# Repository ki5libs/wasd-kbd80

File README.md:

# WASD-kbd80

80% mechanical switch keyboard

## Goal Features
 - QMK-compatibility
 - WASD-libre controller compatibility
 - Mechanical compatibility with existing popular 80% keyboards (i.e XD87 from KRepublic)
 - ANSI, ISO and JIS layouts on one PCB
 - Regulated backlight
 - RGB-highlight
 
 The work is in progress...

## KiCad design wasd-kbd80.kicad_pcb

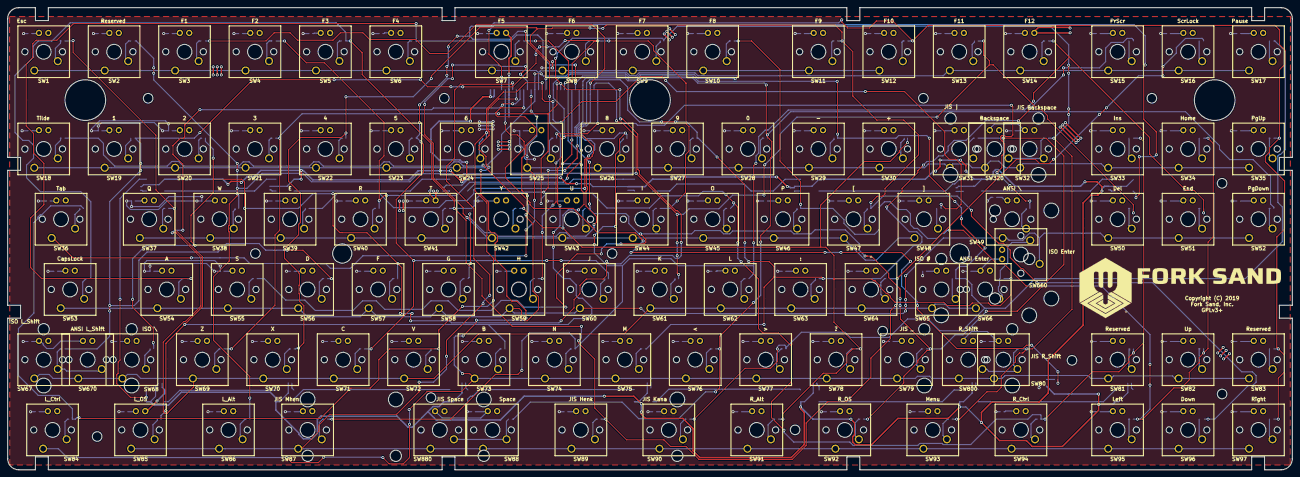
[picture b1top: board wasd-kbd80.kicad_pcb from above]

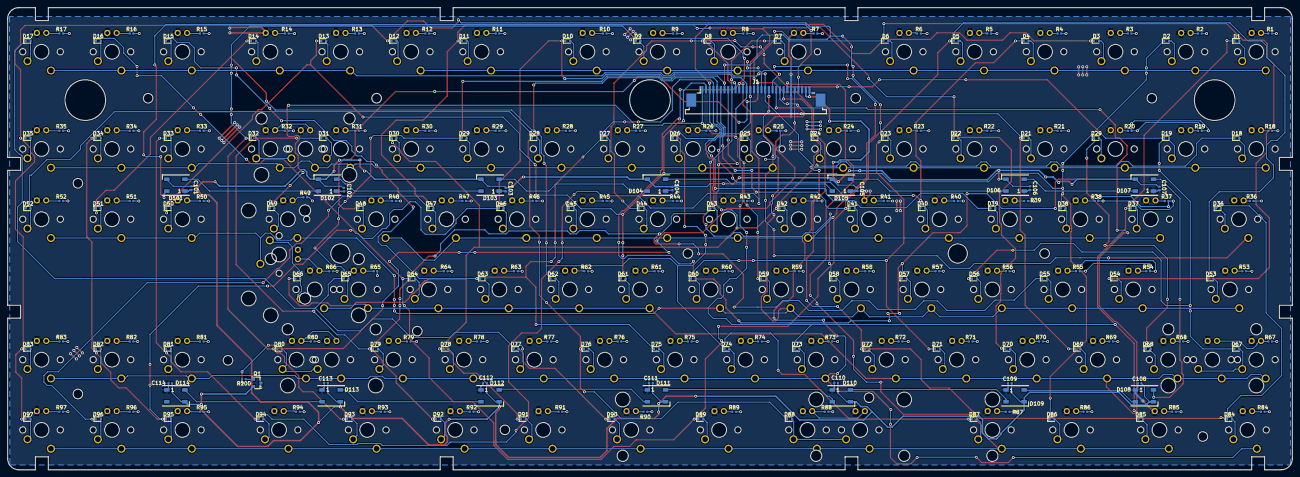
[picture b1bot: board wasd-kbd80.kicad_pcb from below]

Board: 2 copper layers, 347.5 x 125.0 mm, 327 parts (225 on the bottom side), 237 nets.

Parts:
C101, C102, C103, C104, C105, C106, C107, C108, C109, C110, C111, C112, C113, C114: 15pF; C_0402_1005Metric
D1, D2, D3, D4, D5, D6, D7, D8, D9, D10, D11, D12, D13, D14, D15, D16, D17, D18, D19, D20, D21, D22, D23, D24, D25, D26, D27, D28, D29, D30, D31, D32, D33, D34, D35, D36, D37, D38, D39, D40, D41, D42, D43, D44, D45, D46, D47, D48, D49, D50, D51, D52, D53, D54, D55, D56, D57, D58, D59, D60, D61, D62, D63, D64, D65, D66, D67, D68, D69, D70, D71, D72, D73, D74, D75, D76, D77, D78, D79, D80, D81, D82, D83, D84, D85, D86, D87, D88, D89, D90, D91, D92, D93, D94, D95, D96, D97: 1N4148WT; D_SOD-523
D101, D102, D103, D104, D105, D106, D107, D108, D109, D110, D111, D112, D113, D114: WS2812B; LED_WS2812B_PLCC4_5.0x5.0mm_P3.2mm
J1: Conn_01x30; TE_3-84953-0_1x30-1MP_P1.0mm_Horizontal
Q1: BC817; SOT-23
R1, R2, R3, R4, R5, R6, R7, R8, R9, R10, R11, R12, R13, R14, R15, R16, R17, R18, R19, R20, R21, R22, R23, R24, R25, R26, R27, R28, R29, R30, R31, R32, R33, R34, R35, R36, R37, R38, R39, R40, R41, R42, R43, R44, R45, R46, R47, R48, R49, R50, R51, R52, R53, R54, R55, R56, R57, R58, R59, R60, R61, R62, R63, R64, R65, R66, R67, R68, R69, R70, R71, R72, R73, R74, R75, R76, R77, R78, R79, R80, R81, R82, R83, R84, R85, R86, R87, R88, R89, R90, R91, R92, R93, R94, R95, R96, R97: 330R; R_0402_1005Metric
R200: 3K3; R_0402_1005Metric
SW1: Esc; SW_Cherry_MX_1.00u_PCB_LED
SW2, SW81, SW83: Reserved; SW_Cherry_MX_1.00u_PCB_LED
SW3: F1; SW_Cherry_MX_1.00u_PCB_LED
SW4: F2; SW_Cherry_MX_1.00u_PCB_LED
SW5: F3; SW_Cherry_MX_1.00u_PCB_LED
SW6: F4; SW_Cherry_MX_1.00u_PCB_LED
SW7: F5; SW_Cherry_MX_1.00u_PCB_LED
SW8: F6; SW_Cherry_MX_1.00u_PCB_LED
SW9: F7; SW_Cherry_MX_1.00u_PCB_LED
SW10: F8; SW_Cherry_MX_1.00u_PCB_LED
SW11: F9; SW_Cherry_MX_1.00u_PCB_LED
SW12: F10; SW_Cherry_MX_1.00u_PCB_LED
SW13: F11; SW_Cherry_MX_1.00u_PCB_LED
SW14: F12; SW_Cherry_MX_1.00u_PCB_LED
SW15: PrScr; SW_Cherry_MX_1.00u_PCB_LED
SW16: ScrLock; SW_Cherry_MX_1.00u_PCB_LED
SW17: Pause; SW_Cherry_MX_1.00u_PCB_LED
SW18: Tilde; SW_Cherry_MX_1.00u_PCB_LED
SW19: 1; SW_Cherry_MX_1.00u_PCB_LED
SW20: 2; SW_Cherry_MX_1.00u_PCB_LED
SW21: 3; SW_Cherry_MX_1.00u_PCB_LED
SW22: 4; SW_Cherry_MX_1.00u_PCB_LED
SW23: 5; SW_Cherry_MX_1.00u_PCB_LED
SW24: 6; SW_Cherry_MX_1.00u_PCB_LED
SW25: 7; SW_Cherry_MX_1.00u_PCB_LED
SW26: 8; SW_Cherry_MX_1.00u_PCB_LED
SW27: 9; SW_Cherry_MX_1.00u_PCB_LED
SW28: 0; SW_Cherry_MX_1.00u_PCB_LED
SW29: -; SW_Cherry_MX_1.00u_PCB_LED
SW30: +; SW_Cherry_MX_1.00u_PCB_LED
SW31: JIS |; SW_Cherry_MX_1.00u_PCB_LED
SW32: JIS Backspace; SW_Cherry_MX_1.00u_PCB_LED
SW33: Ins; SW_Cherry_MX_1.00u_PCB_LED
SW34: Home; SW_Cherry_MX_1.00u_PCB_LED
SW35: PgUp; SW_Cherry_MX_1.00u_PCB_LED
SW36: Tab; SW_Cherry_MX_1.50u_PCB_LED
SW37: Q; SW_Cherry_MX_1.00u_PCB_LED
SW38: W; SW_Cherry_MX_1.00u_PCB_LED
SW39: E; SW_Cherry_MX_1.00u_PCB_LED
SW40: R; SW_Cherry_MX_1.00u_PCB_LED
SW41: T; SW_Cherry_MX_1.00u_PCB_LED
SW42: Y; SW_Cherry_MX_1.00u_PCB_LED
SW43: U; SW_Cherry_MX_1.00u_PCB_LED
SW44: I; SW_Cherry_MX_1.00u_PCB_LED
SW45: O; SW_Cherry_MX_1.00u_PCB_LED
SW46: P; SW_Cherry_MX_1.00u_PCB_LED
SW47: [; SW_Cherry_MX_1.00u_PCB_LED
SW48: ]; SW_Cherry_MX_1.00u_PCB_LED
SW49: ANSI \; SW_Cherry_MX_1.50u_PCB_LED
SW50: Del; SW_Cherry_MX_1.00u_PCB_LED
SW51: End; SW_Cherry_MX_1.00u_PCB_LED
SW52: PgDown; SW_Cherry_MX_1.00u_PCB_LED
SW53: CapsLock; SW_Cherry_MX_1.75u_PCB_LED
SW54: A; SW_Cherry_MX_1.00u_PCB_LED
SW55: S; SW_Cherry_MX_1.00u_PCB_LED
SW56: D; SW_Cherry_MX_1.00u_PCB_LED
SW57: F; SW_Cherry_MX_1.00u_PCB_LED
SW58: G; SW_Cherry_MX_1.00u_PCB_LED
SW59: H; SW_Cherry_MX_1.00u_PCB_LED
SW60: J; SW_Cherry_MX_1.00u_PCB_LED
SW61: K; SW_Cherry_MX_1.00u_PCB_LED
SW62: L; SW_Cherry_MX_1.00u_PCB_LED
SW63: :; SW_Cherry_MX_1.00u_PCB_LED
SW64: "; SW_Cherry_MX_1.00u_PCB_LED
SW65: ISO #; SW_Cherry_MX_1.00u_PCB_LED
SW66: ANSI Enter; SW_Cherry_MX_2.25u_PCB_LED_Inv
SW67: ISO L_Shift; SW_Cherry_MX_1.00u_PCB_LED
SW68: ISO \; SW_Cherry_MX_1.00u_PCB_LED
SW69: Z; SW_Cherry_MX_1.00u_PCB_LED
SW70: X; SW_Cherry_MX_1.00u_PCB_LED
SW71: C; SW_Cherry_MX_1.00u_PCB_LED
SW72: V; SW_Cherry_MX_1.00u_PCB_LED
SW73: B; SW_Cherry_MX_1.00u_PCB_LED
SW74: N; SW_Cherry_MX_1.00u_PCB_LED
SW75: M; SW_Cherry_MX_1.00u_PCB_LED
SW76: <; SW_Cherry_MX_1.00u_PCB_LED
SW77: >; SW_Cherry_MX_1.00u_PCB_LED
SW78: ?; SW_Cherry_MX_1.00u_PCB_LED
SW79: JIS _; SW_Cherry_MX_1.00u_PCB_LED
SW80: JIS R_Shift; SW_Cherry_MX_1.75u_PCB_LED
SW82: Up; SW_Cherry_MX_1.00u_PCB_LED
SW84: L_Ctrl; SW_Cherry_MX_1.25u_PCB_LED
SW85: L_OS; SW_Cherry_MX_1.25u_PCB_LED
SW86: L_Alt; SW_Cherry_MX_1.25u_PCB_LED
SW87: JIS Mhen; SW_Cherry_MX_1.00u_PCB_LED
SW88: Space; SW_Cherry_MX_6.25u_PCB_LED
SW89: JIS Henk; SW_Cherry_MX_1.25u_PCB_LED
SW90: JIS Kana; SW_Cherry_MX_1.25u_PCB_LED
SW91: R_Alt; SW_Cherry_MX_1.25u_PCB_LED
SW92: R_OS; SW_Cherry_MX_1.25u_PCB_LED
SW93: Menu; SW_Cherry_MX_1.25u_PCB_LED
SW94: R_Ctrl; SW_Cherry_MX_1.25u_PCB_LED
SW95: Left; SW_Cherry_MX_1.00u_PCB_LED
SW96: Down; SW_Cherry_MX_1.00u_PCB_LED
SW97: Right; SW_Cherry_MX_1.00u_PCB_LED
SW320: Backspace; SW_Cherry_MX_2.00u_PCB_LED_Inv
SW660: ISO Enter; SW_Cherry_MX_ISOEnter_PCB_LED_Rot
SW670: ANSI L_Shift; SW_Cherry_MX_2.25u_PCB_LED_Inv
SW800: R_Shift; SW_Cherry_MX_2.75u_PCB_LED_Inv
SW880: JIS Space; SW_Cherry_MX_2.75u_PCB_LED

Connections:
+5V: C101.2, C102.2, C103.2, C104.2, C105.2, C106.2, C107.2, C108.2, C109.2, C110.2, C111.2, C112.2, C113.2, C114.2, D101.1, D102.1, D103.1, D104.1, D105.1, D106.1, D107.1, D108.1, D109.1, D110.1, D111.1, D112.1, D113.1, D114.1, J1.25, J1.28, SW1.4, SW2.4, SW3.4, SW4.4, SW5.4, SW6.4, SW7.4, SW8.4, SW9.4, SW10.4, SW11.4, SW12.4, SW13.4, SW14.4, SW15.4, SW16.4, SW17.4, SW18.4, SW19.4, SW20.4, SW21.4, SW22.4, SW23.4, SW24.4, SW25.4, SW26.4, SW27.4, SW28.4, SW29.4, SW30.4, SW31.4, SW32.4, SW33.4, SW34.4, SW35.4, SW36.4, SW37.4, SW38.4, SW39.4, SW40.4, SW41.4, SW42.4, SW43.4, SW44.4, SW45.4, SW46.4, SW47.4, SW48.4, SW49.4, SW50.4, SW51.4, SW52.4, SW53.4, SW54.4, SW55.4, SW56.4, SW57.4, SW58.4, SW59.4, SW60.4, SW61.4, SW62.4, SW63.4, SW64.4, SW65.4, SW66.4, SW67.4, SW68.4, SW69.4, SW70.4, SW71.4, SW72.4, SW73.4, SW74.4, SW75.4, SW76.4, SW77.4, SW78.4, SW79.4, SW80.4, SW81.4, SW82.4, SW83.4, SW84.4, SW85.4, SW86.4, SW87.4, SW88.4, SW89.4, SW90.4, SW91.4, SW92.4, SW93.4, SW94.4, SW95.4, SW96.4, SW97.4, SW320.4, SW660.4, SW670.4, SW800.4, SW880.4
/32D: D32.2, SW32.2, SW320.2
/32LED: R32.1, SW32.3, SW320.3
/66D: D66.2, SW66.2, SW660.2
/66LED: R66.1, SW66.3, SW660.3
/67D: D67.2, SW67.2, SW670.2
/67LED: R67.1, SW67.3, SW670.3
/80D: D80.2, SW80.2, SW800.2
/80LED: R80.1, SW80.3, SW800.3
/88D: D88.2, SW88.2, SW880.2
/88LED: R88.1, SW88.3, SW880.3
/COL0: J1.17, SW1.1, SW2.1, SW3.1, SW4.1, SW5.1, SW6.1, SW7.1, SW8.1, SW9.1, SW10.1, SW11.1, SW12.1
/COL1: J1.18, SW13.1, SW14.1, SW15.1, SW16.1, SW17.1, SW18.1, SW19.1, SW20.1, SW21.1, SW22.1, SW23.1, SW24.1
/COL2: J1.19, SW25.1, SW26.1, SW27.1, SW28.1, SW29.1, SW30.1, SW31.1, SW32.1, SW33.1, SW34.1, SW35.1, SW36.1, SW320.1
/COL3: J1.20, SW37.1, SW38.1, SW39.1, SW40.1, SW41.1, SW42.1, SW43.1, SW44.1, SW45.1, SW46.1, SW47.1, SW48.1
/COL4: J1.21, SW49.1, SW50.1, SW51.1, SW52.1, SW53.1, SW54.1, SW55.1, SW56.1, SW57.1, SW58.1, SW59.1, SW60.1, SW660.1
/COL5: J1.22, SW61.1, SW62.1, SW63.1, SW64.1, SW65.1, SW66.1, SW67.1, SW68.1, SW69.1, SW70.1, SW71.1, SW72.1, SW670.1
/COL6: J1.23, SW73.1, SW74.1, SW75.1, SW76.1, SW77.1, SW78.1, SW79.1, SW80.1, SW81.1, SW82.1, SW83.1, SW84.1, SW800.1
/COL7: J1.24, SW85.1, SW86.1, SW87.1, SW88.1, SW89.1, SW90.1, SW91.1, SW92.1, SW93.1, SW94.1, SW95.1, SW96.1, SW97.1, SW880.1
/LED_DRV: Q1.3, R1.2, R2.2, R3.2, R4.2, R5.2, R6.2, R7.2, R8.2, R9.2, R10.2, R11.2, R12.2, R13.2, R14.2, R15.2, R16.2, R17.2, R18.2, R19.2, R20.2, R21.2, R22.2, R23.2, R24.2, R25.2, R26.2, R27.2, R28.2, R29.2, R30.2, R31.2, R32.2, R33.2, R34.2, R35.2, R36.2, R37.2, R38.2, R39.2, R40.2, R41.2, R42.2, R43.2, R44.2, R45.2, R46.2, R47.2, R48.2, R49.2, R50.2, R51.2, R52.2, R53.2, R54.2, R55.2, R56.2, R57.2, R58.2, R59.2, R60.2, R61.2, R62.2, R63.2, R64.2, R65.2, R66.2, R67.2, R68.2, R69.2, R70.2, R71.2, R72.2, R73.2, R74.2, R75.2, R76.2, R77.2, R78.2, R79.2, R80.2, R81.2, R82.2, R83.2, R84.2, R85.2, R86.2, R87.2, R88.2, R89.2, R90.2, R91.2, R92.2, R93.2, R94.2, R95.2, R96.2, R97.2
/PWM_IN: J1.26, R200.2
/RGB_IN: D101.4, J1.27
/ROW0: D1.1, D25.1, D37.1, D49.1, D73.1, D85.1, J1.1
/ROW1: D2.1, D13.1, D38.1, D50.1, D61.1, D86.1, J1.2
/ROW2: D3.1, D14.1, D26.1, D51.1, D62.1, D74.1, D87.1, J1.3
/ROW3: D15.1, D27.1, D39.1, D63.1, D75.1, J1.4
/ROW4: D4.1, D28.1, D40.1, D52.1, D76.1, D88.1, J1.5
/ROW5: D5.1, D16.1, D41.1, D53.1, D64.1, D89.1, J1.6
/ROW6: D6.1, D17.1, D29.1, D54.1, D65.1, D77.1, D90.1, J1.7
/ROW7: D18.1, D30.1, D42.1, D66.1, D78.1, D91.1, J1.8
/ROW8: D7.1, D31.1, D43.1, D55.1, D79.1, D92.1, J1.9
/ROW9: D8.1, D19.1, D44.1, D56.1, D67.1, J1.10
/ROW10: D9.1, D20.1, D32.1, D57.1, D68.1, D80.1, D93.1, J1.11
/ROW11: D21.1, D33.1, D45.1, D69.1, D81.1, D94.1, J1.12
/ROW12: D10.1, D34.1, D46.1, D58.1, D82.1, D95.1, J1.13
/ROW13: D11.1, D22.1, D47.1, D59.1, D70.1, D96.1, J1.14
/ROW14: D12.1, D23.1, D35.1, D60.1, D71.1, D83.1, D97.1, J1.15
/ROW15: D24.1, D36.1, D48.1, D72.1, D84.1, J1.16
GND: C101.1, C102.1, C103.1, C104.1, C105.1, C106.1, C107.1, C108.1, C109.1, C110.1, C111.1, C112.1, C113.1, C114.1, D101.3, D102.3, D103.3, D104.3, D105.3, D106.3, D107.3, D108.3, D109.3, D110.3, D111.3, D112.3, D113.3, D114.3, J1.29, J1.30, Q1.2
unnamed: D1.2, SW1.2
unnamed: D2.2, SW2.2
unnamed: D3.2, SW3.2
unnamed: D4.2, SW4.2
unnamed: D5.2, SW5.2
unnamed: D6.2, SW6.2
unnamed: D7.2, SW7.2
unnamed: D8.2, SW8.2
unnamed: D9.2, SW9.2
unnamed: D10.2, SW10.2
unnamed: D11.2, SW11.2
unnamed: D12.2, SW12.2
unnamed: D13.2, SW13.2
unnamed: D14.2, SW14.2
unnamed: D15.2, SW15.2
unnamed: D16.2, SW16.2
unnamed: D17.2, SW17.2
unnamed: D18.2, SW18.2
unnamed: D19.2, SW19.2
unnamed: D20.2, SW20.2
unnamed: D21.2, SW21.2
unnamed: D22.2, SW22.2
unnamed: D23.2, SW23.2
unnamed: D24.2, SW24.2
unnamed: D25.2, SW25.2
unnamed: D26.2, SW26.2
unnamed: D27.2, SW27.2
unnamed: D28.2, SW28.2
unnamed: D29.2, SW29.2
unnamed: D30.2, SW30.2
unnamed: D31.2, SW31.2
unnamed: D33.2, SW33.2
unnamed: D34.2, SW34.2
unnamed: D35.2, SW35.2
unnamed: D36.2, SW36.2
unnamed: D37.2, SW37.2
unnamed: D38.2, SW38.2
unnamed: D39.2, SW39.2
unnamed: D40.2, SW40.2
unnamed: D41.2, SW41.2
unnamed: D42.2, SW42.2
unnamed: D43.2, SW43.2
unnamed: D44.2, SW44.2
unnamed: D45.2, SW45.2
unnamed: D46.2, SW46.2
unnamed: D47.2, SW47.2
unnamed: D48.2, SW48.2
unnamed: D49.2, SW49.2
unnamed: D50.2, SW50.2
unnamed: D51.2, SW51.2
unnamed: D52.2, SW52.2
unnamed: D53.2, SW53.2
unnamed: D54.2, SW54.2
unnamed: D55.2, SW55.2
unnamed: D56.2, SW56.2
unnamed: D57.2, SW57.2
unnamed: D58.2, SW58.2
unnamed: D59.2, SW59.2
unnamed: D60.2, SW60.2
unnamed: D61.2, SW61.2
unnamed: D62.2, SW62.2
unnamed: D63.2, SW63.2
unnamed: D64.2, SW64.2
unnamed: D65.2, SW65.2
unnamed: D68.2, SW68.2
unnamed: D69.2, SW69.2
unnamed: D70.2, SW70.2
unnamed: D71.2, SW71.2
unnamed: D72.2, SW72.2
unnamed: D73.2, SW73.2
unnamed: D74.2, SW74.2
unnamed: D75.2, SW75.2
unnamed: D76.2, SW76.2
unnamed: D77.2, SW77.2
unnamed: D78.2, SW78.2
unnamed: D79.2, SW79.2
unnamed: D81.2, SW81.2
unnamed: D82.2, SW82.2
unnamed: D83.2, SW83.2
unnamed: D84.2, SW84.2
unnamed: D85.2, SW85.2
unnamed: D86.2, SW86.2
unnamed: D87.2, SW87.2
unnamed: D89.2, SW89.2
unnamed: D90.2, SW90.2
unnamed: D91.2, SW91.2
unnamed: D92.2, SW92.2
unnamed: D93.2, SW93.2
unnamed: D94.2, SW94.2
unnamed: D95.2, SW95.2
unnamed: D96.2, SW96.2
unnamed: D97.2, SW97.2
unnamed: D101.2, D102.4
unnamed: D102.2, D103.4
unnamed: D103.2, D104.4
unnamed: D104.2, D105.4
unnamed: D105.2, D106.4
unnamed: D106.2, D107.4
unnamed: D107.2, D108.4
unnamed: D108.2, D109.4
unnamed: D109.2, D110.4
unnamed: D110.2, D111.4
unnamed: D111.2, D112.4
unnamed: D112.2, D113.4
unnamed: D113.2, D114.4
unnamed: Q1.1, R200.1
unnamed: R1.1, SW1.3
unnamed: R2.1, SW2.3
unnamed: R3.1, SW3.3
unnamed: R4.1, SW4.3
unnamed: R5.1, SW5.3
unnamed: R6.1, SW6.3
unnamed: R7.1, SW7.3
unnamed: R8.1, SW8.3
unnamed: R9.1, SW9.3
unnamed: R10.1, SW10.3
unnamed: R11.1, SW11.3
unnamed: R12.1, SW12.3
unnamed: R13.1, SW13.3
unnamed: R14.1, SW14.3
unnamed: R15.1, SW15.3
unnamed: R16.1, SW16.3
unnamed: R17.1, SW17.3
unnamed: R18.1, SW18.3
unnamed: R19.1, SW19.3
unnamed: R20.1, SW20.3
unnamed: R21.1, SW21.3
unnamed: R22.1, SW22.3
unnamed: R23.1, SW23.3
unnamed: R24.1, SW24.3
unnamed: R25.1, SW25.3
unnamed: R26.1, SW26.3
unnamed: R27.1, SW27.3
unnamed: R28.1, SW28.3
unnamed: R29.1, SW29.3
unnamed: R30.1, SW30.3
unnamed: R31.1, SW31.3
unnamed: R33.1, SW33.3
unnamed: R34.1, SW34.3
unnamed: R35.1, SW35.3
unnamed: R36.1, SW36.3
unnamed: R37.1, SW37.3
unnamed: R38.1, SW38.3
unnamed: R39.1, SW39.3
unnamed: R40.1, SW40.3
unnamed: R41.1, SW41.3
unnamed: R42.1, SW42.3
unnamed: R43.1, SW43.3
unnamed: R44.1, SW44.3
unnamed: R45.1, SW45.3
unnamed: R46.1, SW46.3
unnamed: R47.1, SW47.3
unnamed: R48.1, SW48.3
unnamed: R49.1, SW49.3
unnamed: R50.1, SW50.3
unnamed: R51.1, SW51.3
unnamed: R52.1, SW52.3
unnamed: R53.1, SW53.3
unnamed: R54.1, SW54.3
unnamed: R55.1, SW55.3
unnamed: R56.1, SW56.3
unnamed: R57.1, SW57.3
unnamed: R58.1, SW58.3
unnamed: R59.1, SW59.3
unnamed: R60.1, SW60.3
unnamed: R61.1, SW61.3
unnamed: R62.1, SW62.3
unnamed: R63.1, SW63.3
unnamed: R64.1, SW64.3
unnamed: R65.1, SW65.3
unnamed: R68.1, SW68.3
unnamed: R69.1, SW69.3
unnamed: R70.1, SW70.3
unnamed: R71.1, SW71.3
unnamed: R72.1, SW72.3
unnamed: R73.1, SW73.3
unnamed: R74.1, SW74.3
unnamed: R75.1, SW75.3
unnamed: R76.1, SW76.3
unnamed: R77.1, SW77.3
unnamed: R78.1, SW78.3
unnamed: R79.1, SW79.3
unnamed: R81.1, SW81.3
unnamed: R82.1, SW82.3
unnamed: R83.1, SW83.3
unnamed: R84.1, SW84.3
unnamed: R85.1, SW85.3
unnamed: R86.1, SW86.3
unnamed: R87.1, SW87.3
unnamed: R89.1, SW89.3
unnamed: R90.1, SW90.3
unnamed: R91.1, SW91.3
unnamed: R92.1, SW92.3
unnamed: R93.1, SW93.3
unnamed: R94.1, SW94.3
unnamed: R95.1, SW95.3
unnamed: R96.1, SW96.3
unnamed: R97.1, SW97.3

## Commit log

2019-11-24 Set two upper rows
2019-12-02 TODO: ISO Enter rotation
2019-12-18 PCB finished
2019-12-20 Switches for ANSI
2019-12-20 README and renderings
2019-12-22 Logo added
2019-12-22 Fixed diodes footprints, added JCSC numbers
2019-12-22 Fix DRC errors
2019-12-22 FFC connector and logo added
2019-12-22 BOM and positioning file added under version control
2019-12-22 Gerbers added under version control
2019-12-29 3D model added for FPC connector
2020-01-31 Frame mounting holes fixed
2020-02-01 Fixed switches positions for metal frame
2020-02-12 J1 (32 pins) changed to 30 pins for using TE connector
2020-02-24 Project renaming

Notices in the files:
wasd-kbd80.kicad_pcb:
Copyright (C) 2019
GPLv3+
